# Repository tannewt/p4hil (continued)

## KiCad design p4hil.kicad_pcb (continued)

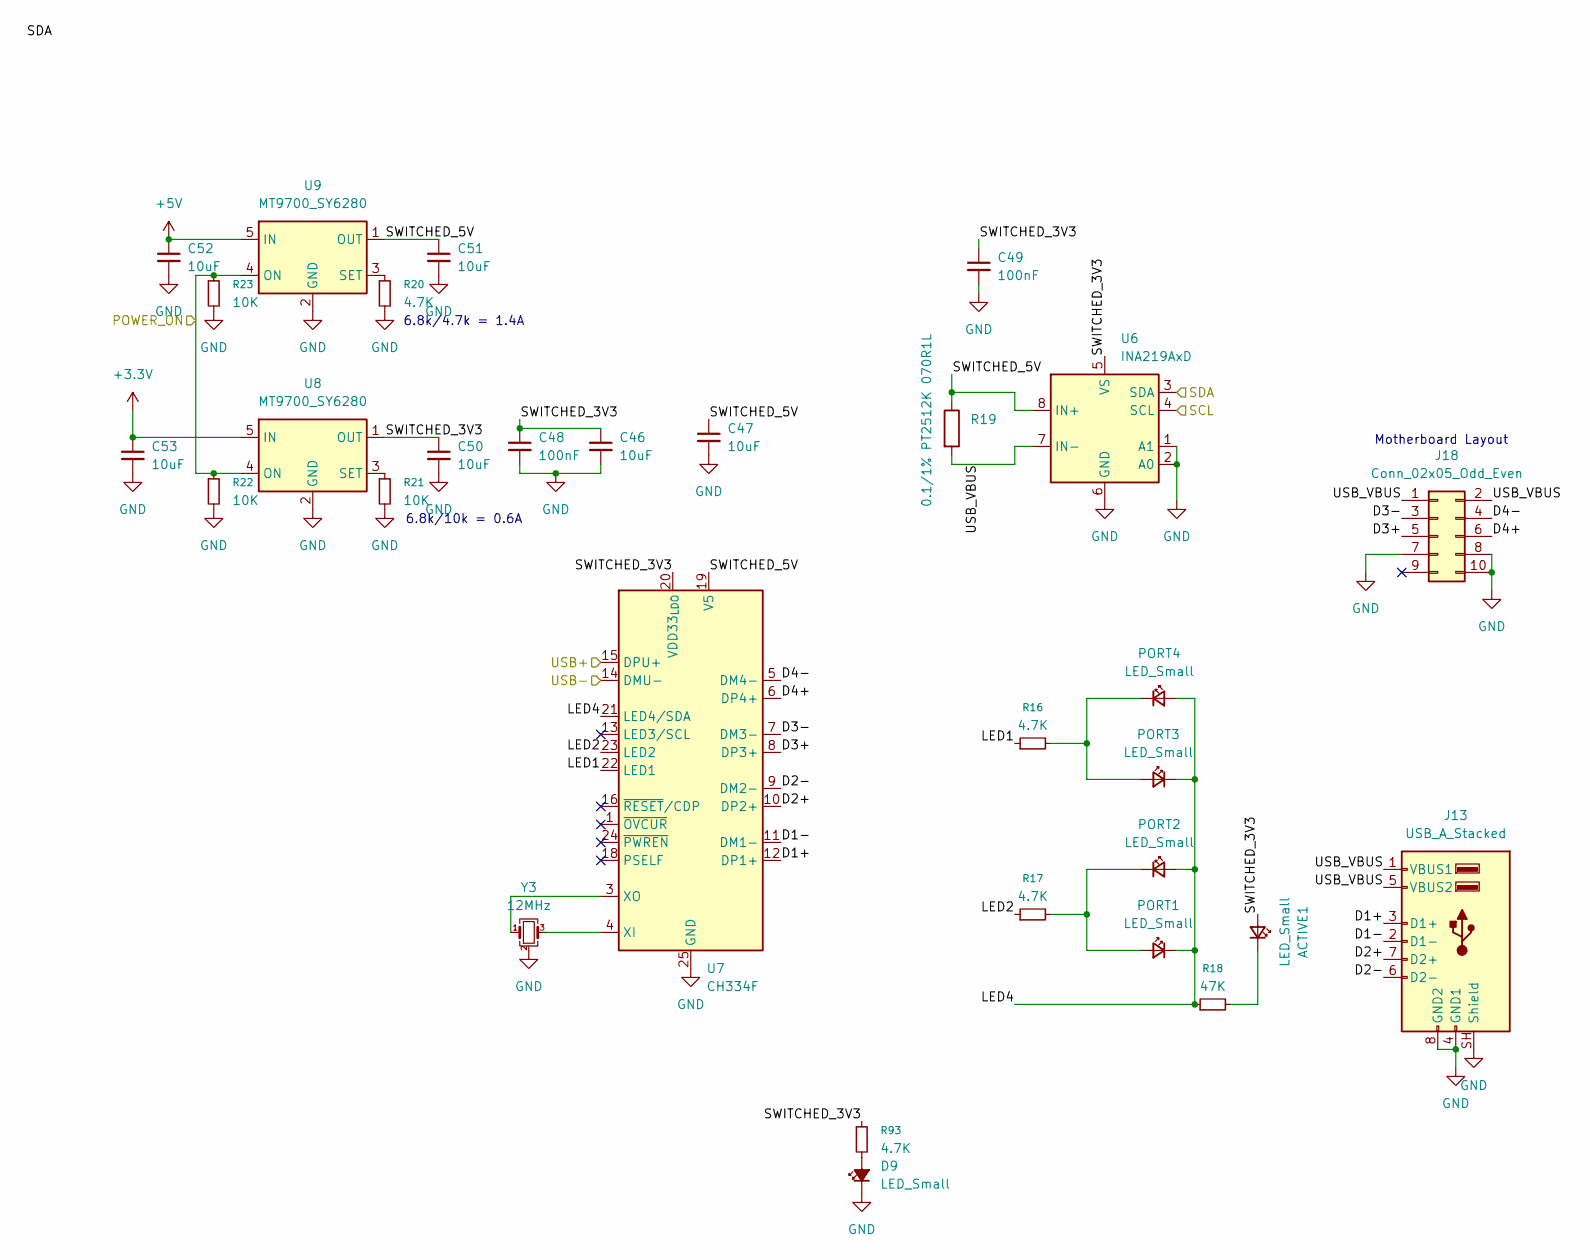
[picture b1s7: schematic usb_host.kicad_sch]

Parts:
ACTIVE1: LED_Small; LED_0603_1608Metric
C46, C47, C50, C51, C52, C53: 10uF; C_0603_1608Metric
C48, C49: 100nF; C_0402_1005Metric
D9: LED_Small; LED_0603_1608Metric
J13: USB_A_Stacked; USB_A_Wuerth_61400826021_Horizontal_Stacked
J18: Conn_02x05_Odd_Even; PinHeader_2x05_P2.54mm_Vertical
PORT1, PORT2, PORT3, PORT4: LED_Small; LED_0603_1608Metric
R16, R17, R20, R93: 4.7K; R_0402_1005Metric
R18: 47K; R_0402_1005Metric
R19: 0.1/1% PT2512K 070R1L; R_2512_6332Metric
R21, R22, R23: 10K; R_0402_1005Metric
U6: INA219AxD; SOIC-8_3.9x4.9mm_P1.27mm
U7: CH334F; QFN-24-1EP_4x4mm_P0.5mm_EP2.7x2.7mm
U8, U9: MT9700_SY6280; SOT-23-5
Y3: 12MHz; Crystal_SMD_3225-4Pin_3.2x2.5mm

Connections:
+3.3V: C53.1, U8.5 (IN); also elsewhere on the board
+5V: C52.1, U9.5 (IN); also elsewhere on the board
/SCL: U6.4 (SCL); also elsewhere on the board
/SDA_BOOT: U6.3 (SDA); also elsewhere on the board
/USB Host/D1+: J13.3 (D1+), U7.12 (DP1+)
/USB Host/D1-: J13.2 (D1-), U7.11 (DM1-)
/USB Host/D2+: J13.7 (D2+), U7.10 (DP2+)
/USB Host/D2-: J13.6 (D2-), U7.9 (DM2-)
/USB Host/D3+: J18.5, U7.8 (DP3+)
/USB Host/D3-: J18.3, U7.7 (DM3-)
/USB Host/D4+: J18.6, U7.6 (DP4+)
/USB Host/D4-: J18.4, U7.5 (DM4-)
/USB Host/LED1: R16.1, U7.22 (LED1)
/USB Host/LED2: R17.1, U7.23 (LED2)
/USB Host/LED4: PORT1.1 (K), PORT2.2 (A), PORT3.1 (K), PORT4.2 (A), R18.1, U7.21 (LED4/SDA)
/USB Host/SWITCHED_3V3: ACTIVE1.2 (A), C46.1, C48.1, C49.1, C50.1, R93.1, U6.5 (VS), U7.20 (VDD33_{LDO}), U8.1 (OUT)
/USB Host/SWITCHED_5V: C47.1, C51.1, R19.1, U6.8 (IN+), U7.19 (V5), U9.1 (OUT)
/USB Host/USB_VBUS: J13.1 (VBUS1), J13.5 (VBUS2), J18.1, J18.2, R19.2, U6.7 (IN-)
/USB_HOST+: U7.15 (DPU+); also elsewhere on the board
/USB_HOST-: U7.14 (DMU-); also elsewhere on the board
/USB_POWER_ON: R22.1, R23.1, U8.4 (ON), U9.4 (ON); also elsewhere on the board
GND: C46.2, C47.2, C48.2, C49.2, C50.2, C51.2, C52.2, C53.2, D9.1 (K), J13.4 (GND1), J13.8 (GND2), J13.SH (Shield), J18.7, J18.8, J18.10, R20.2, R21.2, R22.2, R23.2, U6.1 (A1), U6.2 (A0), U6.6 (GND), U7.25 (GND), U8.2 (GND), U9.2 (GND), Y3.2 (G), Y3.4 (G); also elsewhere on the board
unnamed: ACTIVE1.1 (K), R18.2
unnamed: D9.2 (A), R93.2
unnamed: PORT1.2 (A), PORT2.1 (K), R17.2
unnamed: PORT3.2 (A), PORT4.1 (K), R16.2
unnamed: U7.4 (XI), Y3.3
unnamed: U7.3 (XO), Y3.1
unnamed: R21.1, U8.3 (SET)
unnamed: R20.1, U9.3 (SET)

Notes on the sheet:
6.8k/10k = 0.6A
6.8k/4.7k = 1.4A
Motherboard Layout

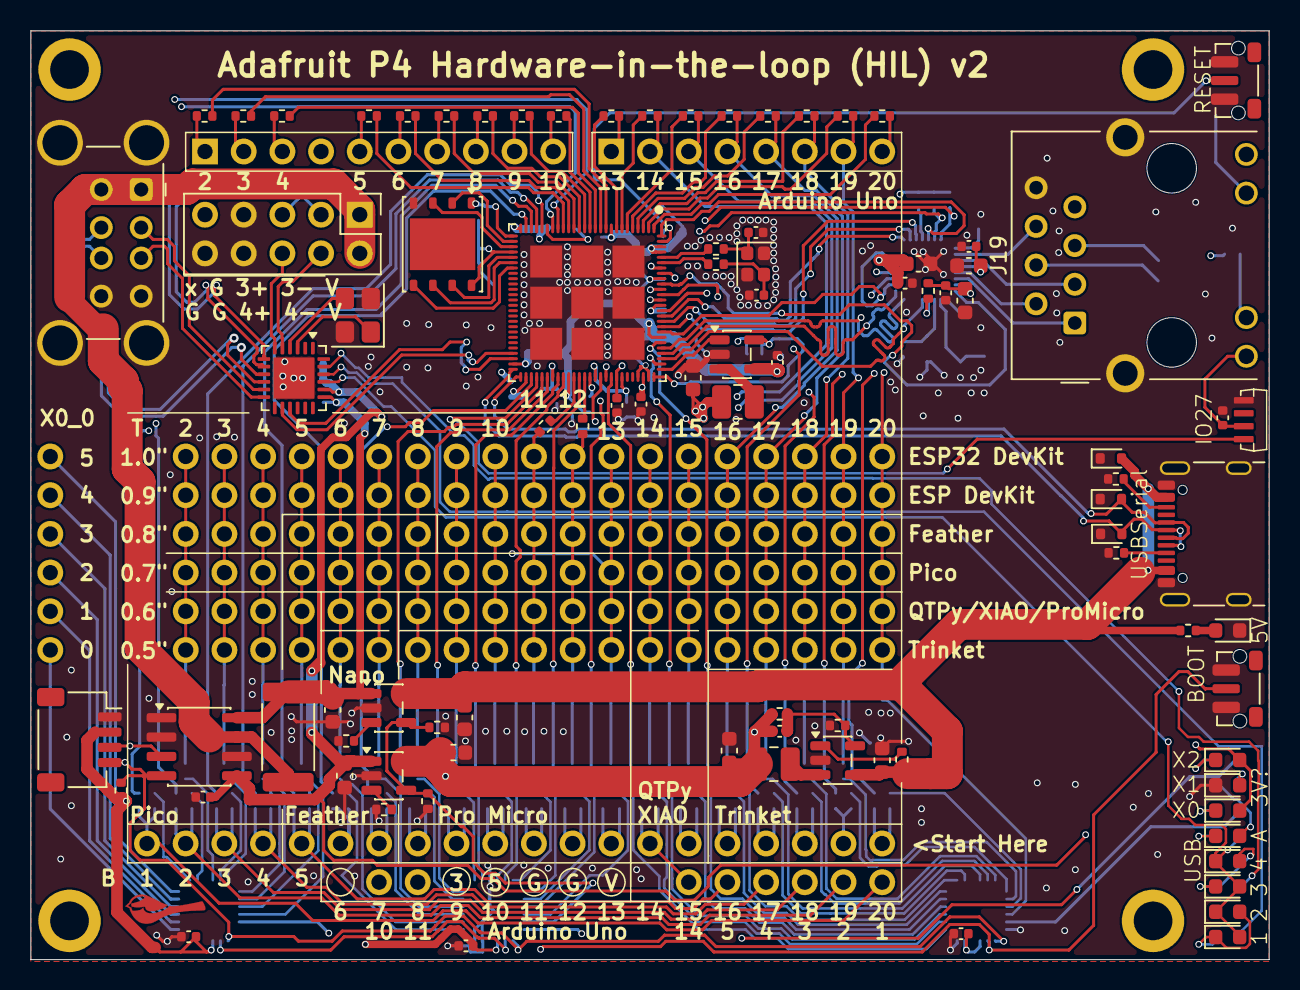
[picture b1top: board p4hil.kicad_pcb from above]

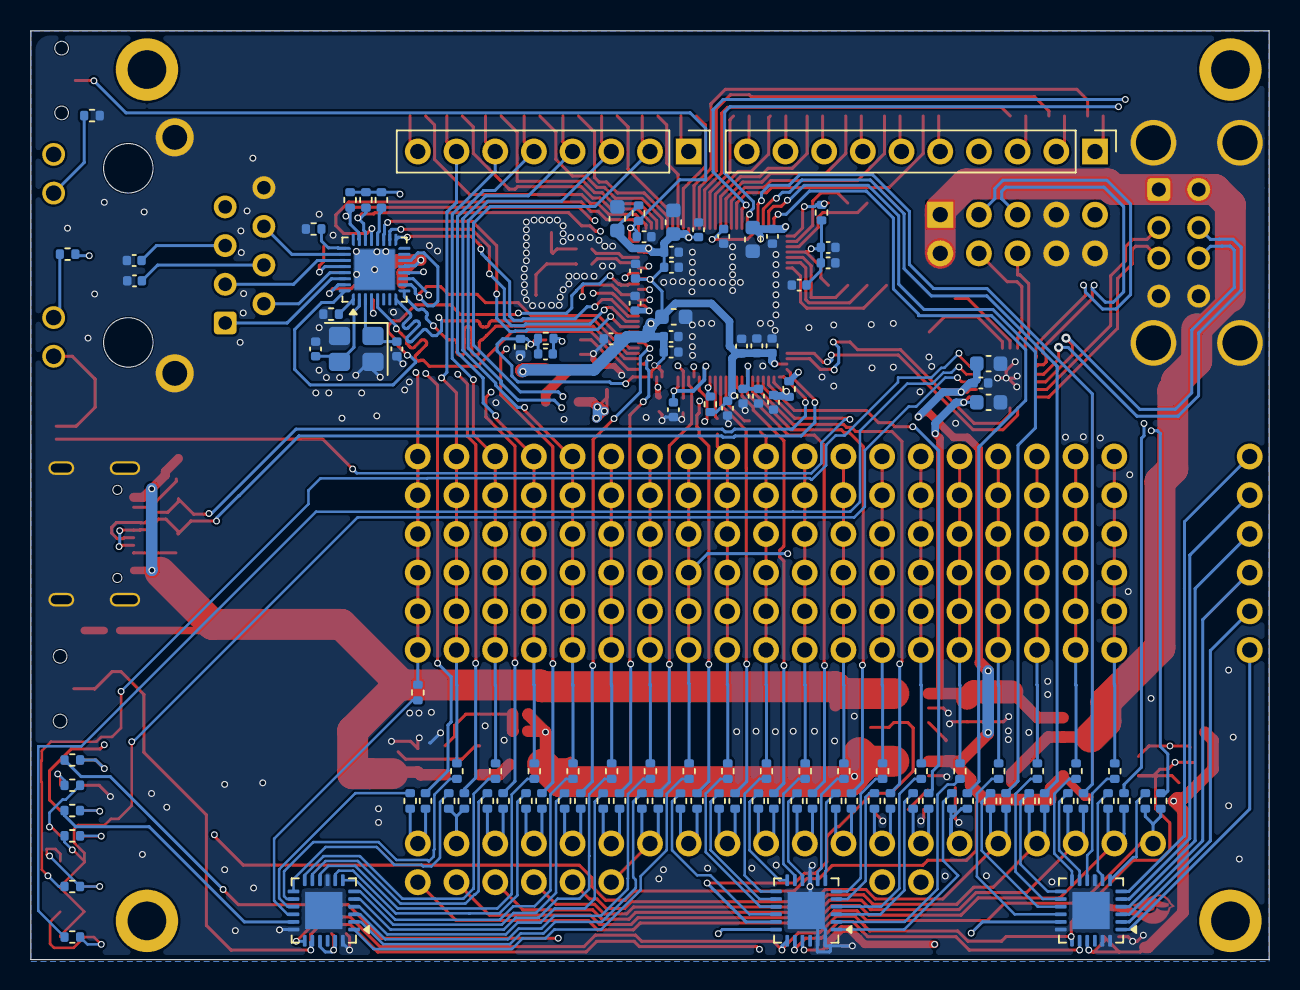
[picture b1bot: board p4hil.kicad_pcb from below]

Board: 4 copper layers, 81.3 x 61.0 mm, 219 parts (120 on the bottom side), 212 nets.

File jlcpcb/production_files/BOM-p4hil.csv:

Comment,Designator,Footprint,LCSC,Quantity
0,"R3,R4,R7",R_0402_1005Metric,C17168,3
0.1/1% PT2512K 070R1L,R19,R_2512_6332Metric,C25466,1
0.1uF,"C10,C13,C15,C16,C17,C19,C22,C23,C26,C28,C3,C31,C32,C4,C54,C6,C60,C61,C62,C7,C9",C_0402_1005Metric,C1525,21
1.5k,R50,R_0402_1005Metric,C25867,1
100K(1%),R28,R_0402_1005Metric,C25741,1
100nF,"C35,C38,C40,C43,C44,C48,C49",C_0402_1005Metric,C1525,7
10K,"R21,R22,R23,R27",R_0402_1005Metric,C25744,4
10k,"R1,R2",R_0402_1005Metric,C25744,2
10nF,C18,C_0402_1005Metric,C15195,1
10uF,"C1,C2,C24,C36,C37,C39,C46,C47,C50,C51,C52,C53,C55,C57,C8",C_0603_1608Metric,C19702,15
12MHz,Y3,Crystal_SMD_3225-4Pin_3.2x2.5mm,C9002,1
12pF,"C12,C14",C_0402_1005Metric,C1547,2
18pF,"C41,C42",C_0402_1005Metric,C1549,2
1k,"R10,R12,R13,R33,R34",R_0402_1005Metric,C11702,5
1uF,"C11,C25,C27,C29,C5",C_0402_1005Metric,C52923,5
2.2K,"R100,R101,R102,R103,R104,R105,R106,R107,R108,R109,R110,R111,R112,R113,R74,R75,R76,R77,R78,R79,R80,R81,R82,R83,R84,R85,R86,R87,R88,R89,R90,R91,R92,R94,R95,R96,R97,R98,R99",R_0402_1005Metric,C25879,39
2.2uH,"L1,L2",L_1008_2520Metric,C279858,2
22.1K(1%),R29,R_0402_1005Metric,C2929993,1
22pF,"C30,C56",C_0402_1005Metric,C1555,2
22uF,C33,C_0603_1608Metric,C59461,1
25Mhz 12pf,Y2,Crystal_SMD_3225-4Pin_3.2x2.5mm,C9006,1
4.7K,"R114,R16,R17,R20,R24,R25,R26,R73,R93",R_0402_1005Metric,C25900,9
4.7uF,"C20,C21",C_0402_1005Metric,C23733,2
40MHz(+-10 ppm) C501798,Y1,Crystal_SMD_2016-4Pin_2.0x1.6mm,C501798,1
47K,R18,R_0402_1005Metric,C25792,1
499k,"R5,R6",R_0402_1005Metric,C137971,2
5.1K(1%),"R30,R31",R_0402_1005Metric,C25905,2
6.19K,R11,R_0402_1005Metric,C25914,1
CH334F,U7,QFN-24-1EP_4x4mm_P0.5mm_EP2.7x2.7mm,C5187527,1
Conn_01x04,J14,JST_SH_SM04B-SRSS-TB_1x04-1MP_P1.00mm_Horizontal,C160404,1
INA219AxD,U6,SOIC-8_3.9x4.9mm_P1.27mm,C138706,1
IPGRI,U4,QFN-32-1EP_4x4mm_P0.4mm_EP2.65x2.65mm,C703537,1
LED_Small,"ACTIVE1,D5,D6,D8,D9,PORT1,PORT2,PORT3,PORT4",LED_0603_1608Metric,C84267,9
LESD5D5.0CT1G,"D2,D3,D4",D_SOD-523,C5274290,3
MT9700_SY6280,"U8,U9",SOT-23-5,C55136,2
PI4IOE5V9535ZDEX,"U11,U12,U5",VQFN-24-1EP_4x4mm_P0.5mm_EP2.45x2.45mm,C3188776,3
RJ45_Hanrun_HR911105A_Horizontal,J19,RJ45_Hanrun_HR911105A_Horizontal,C12074,1
R_Protect,"R14,R15,R35,R36,R37,R38,R39,R40,R41,R42,R43,R44,R45,R46,R47,R48,R49,R51,R52,R53,R54,R55,R56,R57,R58,R59,R60,R61,R62,R63,R64,R65,R66,R67,R68,R69,R70,R8,R9",R_0402_1005Metric,C17168,39
SW_Push,"SW1,SW2",SW_Push_1P1T-MP_NO_Horizontal_Alps_SKRTLAE010,C110293,2
TLV62569DBV,"U10,U3",SOT-23-5,C141836,2
USB_A_Stacked,J13,USB_A_Wuerth_61400826021_Horizontal_Stacked,C456021,1
USB_C_Receptacle_USB2.0_16P,J3,USB_C_Receptacle_HRO_TYPE-C-31-M-31,C2760486,1
W25Q128JVS,U1,WSON-8-1EP_6x5mm_P1.27mm_EP3.4x4.3mm,C190862,1
WS2812B,D1,WS2812B-4020,C965557,1
~,U2,ESP32-P4,C22387510,1

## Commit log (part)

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2026-04-23 Initial HIL brainstorming
2026-04-27 More brainstorming
2026-04-28 More schematic work. Mostly on Ethernet
2026-04-28 More USB schematic work
2026-04-30 Getting close. Fault circuit left
2026-04-30 Fault circuit getting close
2026-05-01 where I'm at. fault not needed
2026-05-01 Remove fault stuff
2026-05-04 Pack things in
2026-05-04 Drop T20'
2026-05-05 Swirly gridify
2026-05-05 more routing
2026-05-05 Lots more routing
2026-05-05 close to routed
2026-05-06 gah, need i2c expander for pull control
2026-05-06 clean drc
2026-05-06 silkscreen
2026-05-08 Polish for v1
2026-05-08 Connect flash VDD and more silkscreen
2026-06-03 Start v2
2026-06-04 Add IO expanders, swap ethernet and move USB LEDs
2026-06-09 To order
